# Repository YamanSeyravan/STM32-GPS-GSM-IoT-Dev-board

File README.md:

# STM32-GPS-GSM-IoT-Dev-board
IoT development board with embedded GPS+GSM system for students and R&D projects.
This project is not fully ready yet for Sch, Gerber and assembly files or any info contact me.

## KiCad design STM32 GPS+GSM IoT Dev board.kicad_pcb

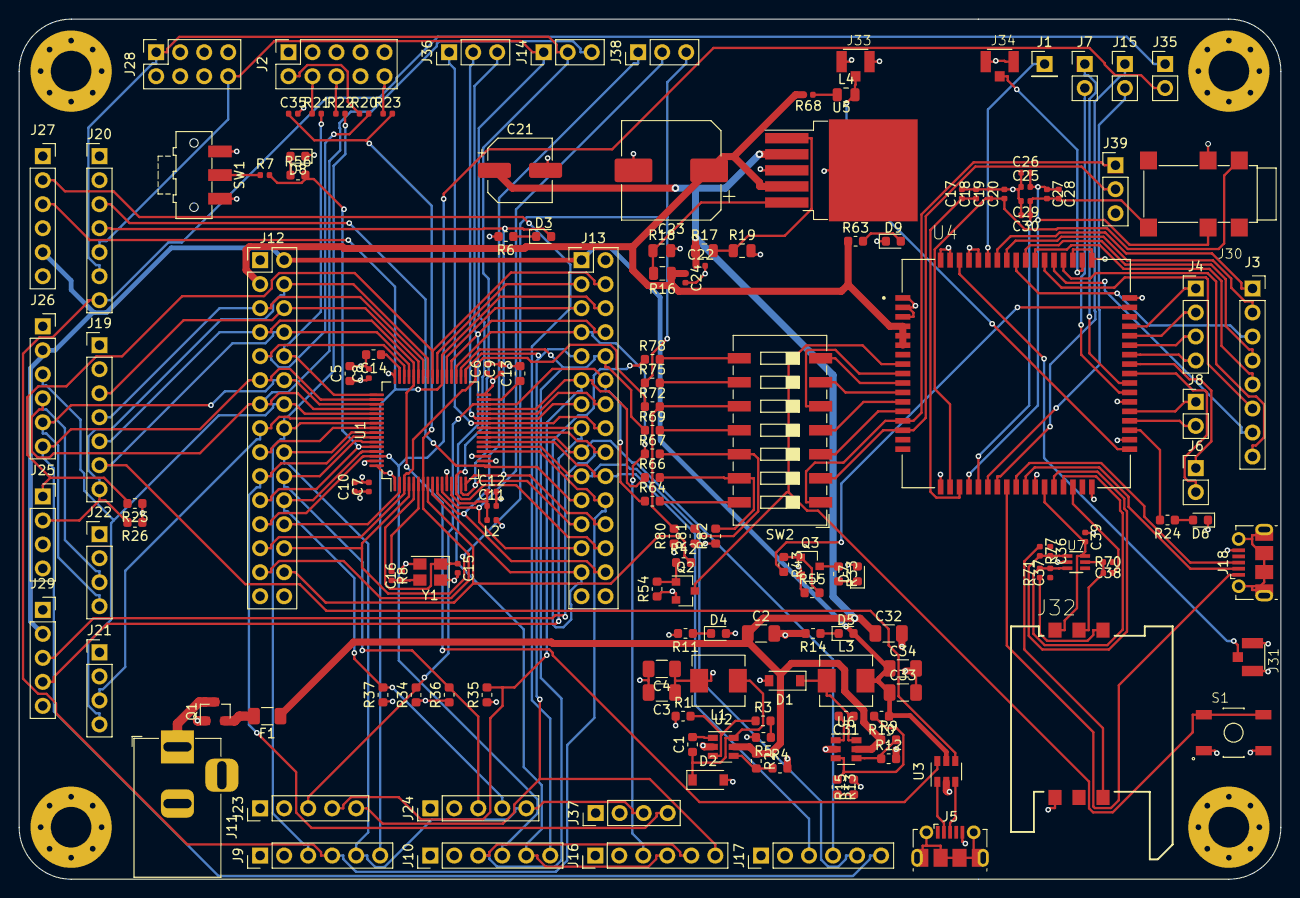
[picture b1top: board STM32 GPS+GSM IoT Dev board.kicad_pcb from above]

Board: 4 copper layers, 133.5 x 91.0 mm, 161 parts (0 on the bottom side), 149 nets.

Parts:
C1, C31: 10n; C_0603_1608Metric
C2, C3, C4, C32, C33, C34: 10u; C_1206_3216Metric
C5: 4u7; C_0603_1608Metric
C6, C7, C8, C9, C10, C35: 100n; C_0402_1005Metric
C11: 1u; C_0402_1005Metric
C12: 10n; C_0402_1005Metric
C13, C14: 2u2; C_0603_1608Metric
C15, C16: 12p; C_0402_1005Metric
C17, C20, C25, C27, C29: 10pf; C_0402_1005Metric
C18, C19, C26, C28, C30: 30pf; C_0402_1005Metric
C21: 100uf; CP_Elec_6.3x7.7
C22: 1uf; C_0402_1005Metric
C23: 330uf; CP_Elec_10x10
C24, C39: 100nf; C_0402_1005Metric
C36, C37, C38: 33pf; C_0402_1005Metric
D1, D2: B5819W; D_SOD-123
D3: BLUE; D_0603_1608Metric
D4, D5: RED; D_0603_1608Metric
D6, D7: LED_Small; LED_0603_1608Metric
D8: LED_BOOT; LED_0603_1608Metric
D9: PWR; LED_0603_1608Metric
F1: 12H1300C; Fuse_1206_3216Metric
H1, H2, H3, H4: MountingHole_Pad; MountingHole_4.3mm_M4_Pad_Via
J1: RF; PinHeader_1x01_P2.54mm_Vertical
J2: SWD; PinSocket_2x05_P2.54mm_Vertical
J3: Key_Pad_Port; PinSocket_1x08_P2.54mm_Vertical
J4: PCM; PinHeader_1x04_P2.54mm_Vertical
J5, J18: USB_B_Micro; USB_Micro-B_Molex-105017-0001
J6: GPIO; PinHeader_1x02_P2.54mm_Vertical
J7: PWM; PinHeader_1x02_P2.54mm_Vertical
J8: I2C; PinHeader_1x02_P2.54mm_Vertical
J9: I2S3; PinHeader_1x06_P2.54mm_Vertical
J10: I2S2; PinHeader_1x06_P2.54mm_Vertical
J11: Barrel_Jack; BarrelJack_Horizontal
J12: Upper Half; PinHeader_2x15_P2.54mm_Vertical
J13: Lower Half; PinHeader_2x15_P2.54mm_Vertical
J14: ADC1; PinHeader_1x03_P2.54mm_Vertical
J15: ADC; PinHeader_1x02_P2.54mm_Vertical
J16: SPI2; PinHeader_1x06_P2.54mm_Vertical
J17: SPI1; PinHeader_1x06_P2.54mm_Vertical
J19: USART1; PinHeader_1x07_P2.54mm_Vertical
J20: USART2; PinHeader_1x07_P2.54mm_Vertical
J21: UART5; PinHeader_1x04_P2.54mm_Vertical
J22: UART4; PinHeader_1x04_P2.54mm_Vertical
J23: I2C2; PinHeader_1x05_P2.54mm_Vertical
J24: I2C1; PinHeader_1x05_P2.54mm_Vertical
J25: LCD; PinSocket_1x04_P2.54mm_Vertical
J26: SD_CARD; PinSocket_1x06_P2.54mm_Vertical
J27: Bluetooth; PinSocket_1x06_P2.54mm_Vertical
J28: WIFI; PinSocket_2x04_P2.54mm_Vertical
J29: Joystick; PinSocket_1x05_P2.54mm_Vertical
J30: SJ-43504-SMT-TR; CUI_SJ2-35464A-SMT-TR
J31: U.FL-R-SMT-GSM; HRS_U.FL-R-SMT(01)
J32: SIM5051-6-0-18-00-X_REVF; GCT_SIM5051-6-0-18-00-X_REVF
J33: U.FL-R-SMT-GPS; HRS_U.FL-R-SMT(01)
J34: U.FL-R-SMT-BT; HRS_U.FL-R-SMT(01)
J35: DAC; PinHeader_1x02_P2.54mm_Vertical
J36: ADC2; PinHeader_1x03_P2.54mm_Vertical
J37: CAN2; PinHeader_1x04_P2.54mm_Vertical
J38: ADC3; PinHeader_1x03_P2.54mm_Vertical
J39: SIM_UART_TTL; PinHeader_1x03_P2.54mm_Vertical
L1, L3: 10u; L_Sunlord_MWSA0518_5.4x5.2mm
L2: 39n; L_0402_1005Metric
L4: 47uh; L_0805_2012Metric
Q1: AO3401A; SOT-23
Q2, Q3: BC847; SOT-23
R1, R10, R54, R55: 47k; R_0603_1608Metric
R2, R9: 100k; R_0603_1608Metric
R3: 15k; R_0603_1608Metric
R4, R12: 68k; R_0603_1608Metric
R5: 270; R_0603_1608Metric
R6: 1k5; R_0603_1608Metric
R7: 10k; R_0402_1005Metric
R8: 47; R_0402_1005Metric
R11, R14, R24, R33, R56: 1k; R_0603_1608Metric
R13: 6.8k; R_0603_1608Metric
R15: 2.2k; R_0603_1608Metric
R16: 100k; R_0805_2012Metric
R17: 12k; R_0805_2012Metric
R18: 47k; R_0805_2012Metric
R19: 4k; R_0805_2012Metric
R20, R21, R22, R23, R68, R70, R71, R77: 22; R_0402_1005Metric
R25, R26, R34, R35, R36, R37: 2k2; R_0603_1608Metric
R42, R43: 4.7k; R_0603_1608Metric
R63, R64, R66, R67, R69, R72, R75, R78: 1K; R_0603_1608Metric
R80, R81, R82: 5.6K; R_0603_1608Metric
S1: TL3342F160QG; SW_TL3342F160QG
SW1: SW_SPDT; SW_SPDT_CK-JS102011SAQN
SW2: SW_DIP_x07; SW_DIP_SPSTx07_Slide_9.78x19.96mm_W8.61mm_P2.54mm
U1: STM32F405RGT6; LQFP-64_10x10mm_P0.5mm
U2, U6: MP2359DJ-LF-Z; SOT-23-6
U3: USBLC6-2SC6; SOT-23-6
U4: SIM808; XCVR_SIM808
U5: MIC29302WU; TO-263-5_TabPin3
U7: SMF05CT1G; SOT65P210X110-6N
Y1: 16MHz; Crystal_SMD_3225-4Pin_3.2x2.5mm

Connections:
1PPS: R24.2, U4.37
+3.3VA: C11.1, C12.1, L2.2, U1.13
+3V3: C3.1, C4.1, C5.1, C6.1, C7.1, C8.1, C9.1, C10.1, D4.2, D7.2, J2.3, J9.1, J10.1, J12.30, J13.29, J16.1, J17.1, J19.1, J20.1, J21.1, J22.1, J23.1, J24.1, J25.3, J28.3, J28.7, J37.1, L1.2, L2.1, R1.1, R25.1, R26.1, R34.1, R35.1, R36.1, R37.1, SW1.1, U1.1, U1.19, U1.32, U1.48, U1.64
+5V: C33.1, C34.1, D5.2, J12.2, J13.1, J26.2, J27.5, J29.2, L3.2, R10.1, U3.5
+12V: J11.1, Q1.3
BOOT0: J12.21, R7.2, R56.2, U1.60
BT_ANT: J34.3, U4.53
GND: C2.2, C3.2, C4.2, C5.2, C6.2, C7.2, C8.2, C9.2, C10.2, C11.2, C12.2, C13.2, C14.2, C15.2, C16.2, C17.2, C18.2, C19.2, C20.2, C21.2, C22.2, C23.2, C24.2, C25.1, C26.1, C29.2, C30.2, C32.2, C33.2, C34.2, C35.2, C39.1, D1.2, D2.2, D6.1, D8.1, D9.1, H1.1, H2.1, H3.1, H4.1, J2.5, J2.7, J5.5, J9.2, J10.2, J11.2, J12.1, J12.29, J13.2, J13.30, J16.2, J17.2, J18.5, J19.2, J20.2, J21.2, J22.2, J23.2, J24.2, J25.4, J26.1, J27.4, J28.2, J29.1, J30.4, J31.1, J31.2, J32.C5, J33.1, J33.2, J34.1, J34.2, J37.2, J39.3, Q1.1, Q2.2, Q3.2, R4.2, R5.2, R6.2, R11.2, R12.2, R14.2, R15.2, R18.2, R19.2, R54.1, R55.1, R80.1, R81.1, R82.1, S1.1, S1.2, SW1.3, U1.12, U1.18, U1.63, U2.2, U3.2, U4.1, U4.2, U4.3, U4.18, U4.28, U4.34, U4.36, U4.40, U4.51, U4.52, U4.54, U4.64, U4.65, U4.67, U4.68, U5.3, U6.2, U7.2, Y1.2, Y1.4
GPS_ANT: J33.3, L4.2, U4.35
GSM_ANT: J31.3, U4.66
HSE_IN: C15.1, U1.5, Y1.1
HSE_OUT: R8.1, U1.6
I2C1_SCL: J12.19, J37.4, U1.58
I2C1_SDA: J12.20, J24.3, R36.2, U1.59
LED_STATUS: D3.2, J13.24, J20.4, U1.16
Left: C27.2, C28.2, C29.1, C30.1, J30.2, U4.22
MIC1N: C17.1, C18.1, U4.20
MIC1P: C19.1, C20.1, J30.1, U4.19
NETLIGHT: R43.2, U4.50
NRST: C35.1, J12.27, R23.2, U1.7
unnamed: C1.1, D2.1, L1.1, U2.6
unnamed: C1.2, U2.1
unnamed: C13.1, U1.31
unnamed: C14.1, U1.47
unnamed: C16.1, R8.2, Y1.3
unnamed: C31.1, D1.1, L3.1, U6.6
unnamed: C31.2, U6.1
unnamed: C38.2, J32.C2, R70.1, U7.5
unnamed: D3.1, R6.1
unnamed: D4.1, R11.1
unnamed: D5.1, R14.1
unnamed: D6.2, R24.1
unnamed: D7.1, R33.2
unnamed: D8.2, R56.1
unnamed: D9.2, R63.2
unnamed: F1.2, Q1.2
unnamed: J1.1, U4.63
unnamed: J2.2, R20.1
unnamed: J2.4, R21.1
unnamed: J2.6, R22.1
unnamed: J2.10, R23.1
unnamed: J3.1, U4.62
unnamed: J3.2, U4.61
unnamed: J3.3, U4.60
unnamed: J3.4, U4.59
unnamed: J3.5, U4.58
unnamed: J3.6, U4.57
unnamed: J3.7, U4.56
unnamed: J3.8, U4.55
unnamed: J4.1, U4.48
unnamed: J4.2, U4.47
unnamed: J4.3, U4.46
unnamed: J4.4, U4.45
unnamed: J6.1, U4.44
unnamed: J6.2, U4.43
unnamed: J7.1, U4.42
unnamed: J7.2, U4.41
unnamed: J8.1, U4.39
unnamed: J8.2, U4.38
unnamed: J15.1, U4.24
unnamed: J15.2, U4.23
unnamed: J32.C3, R71.1
unnamed: J32.C7, R77.1
unnamed: L4.1, R68.1
unnamed: Q2.1, R42.1, R54.2
unnamed: Q3.1, R43.1, R55.2
unnamed: Q3.3, R33.1
unnamed: R1.2, R3.1, U2.3
unnamed: R2.2, R4.1, U2.4
unnamed: R3.2, R5.1
unnamed: R7.1, SW1.2
unnamed: R10.2, R13.1, U6.3
unnamed: R9.2, R12.1, U6.4
unnamed: R13.2, R15.1
unnamed: R16.2, R18.1, U5.5
unnamed: R17.2, R19.1, U5.1
unnamed: R64.2, SW2.14
unnamed: R66.2, R82.2, SW2.13
unnamed: R67.2, R81.2, SW2.12
unnamed: R69.2, SW2.11
unnamed: R72.2, R80.2, SW2.10
unnamed: R75.2, SW2.9
unnamed: R78.2, SW2.8
PA0: J13.26, J14.1, J20.5, J28.8, U1.14
PA1: J13.23, J14.2, J20.6, J28.1, U1.15
PA3: J13.21, J20.3, U1.17
PA4: J9.4, J13.22, J20.7, J35.1, U1.20
PA5: J13.19, J17.5, U1.21
PA6: J13.20, J17.3, U1.22
PA7: J13.17, J17.4, U1.23
PA8: J12.4, J19.7, J25.2, R26.2, U1.41
PA9: J12.5, J19.4, U1.42
PA10: J12.6, J19.3, U1.43
PA11: J12.7, J19.5, U1.44, U3.6
PA12: J12.8, J19.6, U1.45, U3.4
PA13: J12.9, R20.2, U1.46
PA14: J12.10, R21.2, U1.49
PA15: J12.11, J17.6, J26.6, U1.50
PB0: J13.16, J36.1, U1.26
PB1: J13.13, J36.2, U1.27
PB2: J13.14, U1.28
PB3: J9.3, J12.16, R22.2, U1.55
PB4: J12.17, U1.56
PB5: J9.5, J12.18, J24.5, J37.3, U1.57
PB8: J12.22, J24.4, R37.2, U1.61
PB9: J10.4, J12.23, J35.2, U1.62
PB10: J13.11, J23.4, R35.2, R66.1, U1.29
PB11: J13.12, J23.3, R34.2, R64.1, U1.30
PB12: J13.9, J16.6, J23.5, U1.33
PB13: J10.3, J13.10, J16.5, R69.1, U1.34
PB14: J13.7, J16.3, R67.1, U1.35
PB15: J10.5, J13.8, J16.4, J36.3, U1.36
PC0: J12.28, R42.2, U1.8
PC1: J13.27, R78.1, U1.9
PC2: J13.28, J38.1, U1.10
PC3: J13.25, J38.2, U1.11
PC4: J13.18, J29.3, U1.24
PC5: J13.15, J29.4, U1.25
PC6: J10.6, J13.5, J27.2, U1.37
PC7: J9.6, J13.6, J27.3, U1.38
PC8: J13.3, U1.39
PC9: J13.4, J25.1, R25.2, U1.40
PC10: J12.12, J22.4, J26.5, U1.51
PC11: J12.13, J14.3, J22.3, J26.4, U1.52
PC12: J12.14, J21.4, J26.3, U1.53
PC13: J12.24, U1.2
PC14: J12.25, R72.1, U1.3
PC15: J12.26, J38.3, R75.1, U1.4
PD2: J12.15, J21.3, U1.54
PWRKEY: Q2.3, S1.3, S1.4, U4.8
Protected_12V: C2.1, C21.1, C22.1, C32.1, F1.1, R2.1, R9.1, R17.1, U2.5, U5.2, U6.5
Right: C25.2, C26.2, C27.1, C28.1, J30.3, U4.21
SIM_CLK: C37.2, R71.2, U4.31, U7.3
SIM_CTS: SW2.4, U4.12
SIM_DATA: C36.2, R77.2, U4.30, U7.1
SIM_DCD: SW2.6, U4.11
SIM_DTR: SW2.5, U4.9
SIM_RING: SW2.7, U4.10
SIM_RST: R70.2, U4.32
SIM_RTS: SW2.3, U4.13
SIM_RXD: J39.2, SW2.2, U4.15
SIM_TXD: J39.1, SW2.1, U4.14
SIM_USB_D+: J18.3, U4.26
SIM_USB_D-: J18.2, U4.27
SIM_USB_VBUS: J18.1, U4.25
SIM_VDD: C39.2, J32.C1, U4.29, U7.6
USB_CONN_D+: J5.3, U3.3
USB_CONN_D-: J5.2, U3.1
VBAT: C23.1, C24.1, J12.3, R16.1, R63.1, R68.2, U4.4, U4.5, U4.6, U5.4

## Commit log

2021-02-18 Readme update
    info added
